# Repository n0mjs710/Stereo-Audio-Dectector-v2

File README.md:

# Stereo-Audio-Dectector-v2

Stereo Audio Detector: Precision rectifiers and integrators for driving VU displays.

This analog cirucit is intended to handle "front-end" conditioning for VU meters, but could be used for any low-frequency analog AC signal where the envelope of the waveform is of interest. The schmatic has several notes for changing values for different purposes.

The original intention was as VU meter front-end for Arduino or Teensy microcontrollers to use to "talk" to the Stereo VU Meter display, also published under my github account.

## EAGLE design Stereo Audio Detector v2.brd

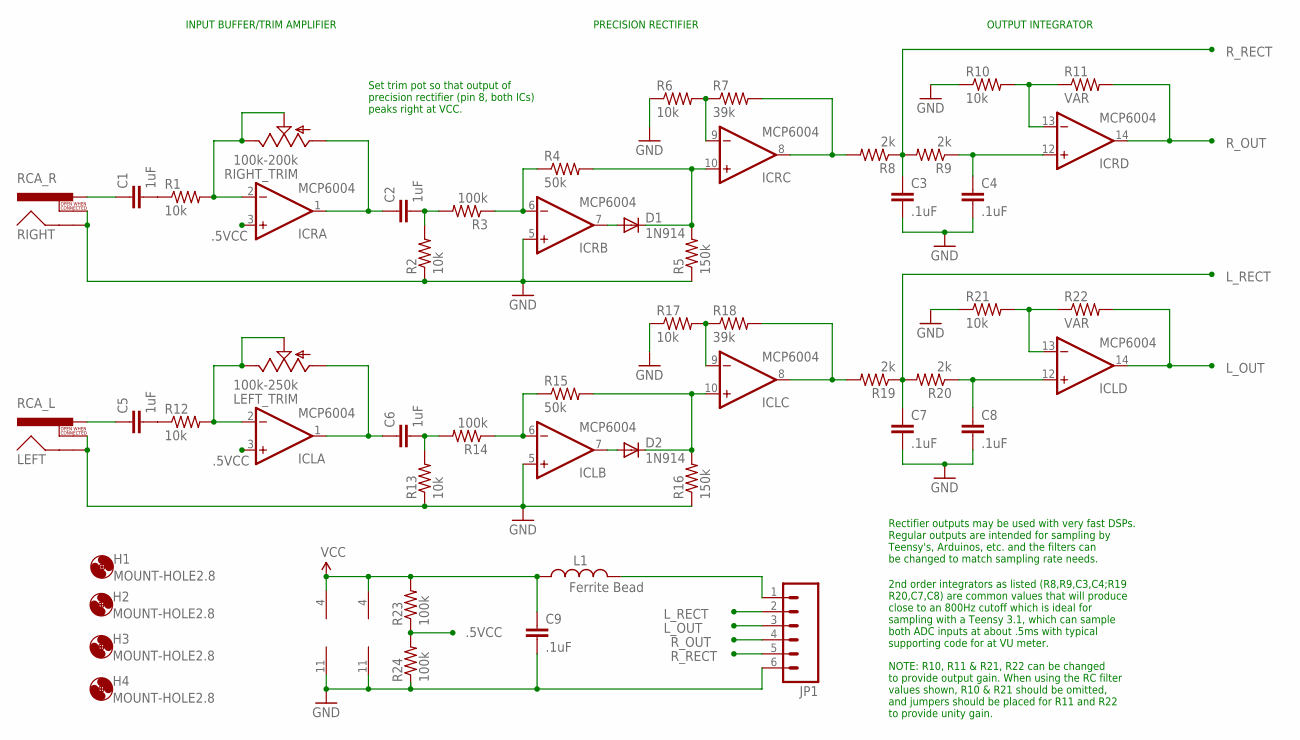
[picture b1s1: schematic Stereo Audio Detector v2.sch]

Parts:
C1, C2, C5, C6: 1uF; C2.5-2
C3, C4, C7, C8, C9: .1uF; C2.5-2
D1, D2: 1N914; D-5
H1, H2, H3, H4: MOUNT-HOLE2.8; 2,8
ICL: MCP6004; DIL14
ICR: MCP6004; DIL14
JP1: M06SIP; 1X06
L1: Ferrite Bead; AXIAL-0.3
LEFT: RCA_L; RCA
LEFT_TRIM: 100k-250k; CT6
R1, R2, R6, R10, R12, R13, R17, R21: 10k; AXIAL-0.3
R3, R14, R23, R24: 100k; AXIAL-0.3
R4, R15: 50k; AXIAL-0.3
R5, R16: 150k; AXIAL-0.3
R7, R18: 39k; AXIAL-0.3
R8, R9, R19, R20: 2k; AXIAL-0.3
R11, R22: VAR; AXIAL-0.3
RIGHT: RCA_R; RCA
RIGHT_TRIM: 100k-200k; CT6

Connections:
.5VCC: ICL.3 (+IN), ICR.3 (+IN), R23.P$1 (1), R24.P$2 (2)
GND: C3.2, C4.2, C7.2, C8.2, C9.2, ICL.5 (+IN), ICL.11 (V-), ICR.5 (+IN), ICR.11 (V-), JP1.6, LEFT.SHELL, LEFT.SWITCH, R2.P$1 (1), R5.P$1 (1), R6.P$1 (1), R10.P$1 (1), R13.P$1 (1), R16.P$1 (1), R17.P$1 (1), R21.P$1 (1), R24.P$1 (1), RIGHT.SHELL, RIGHT.SWITCH
IN_L: C1.1, RIGHT.PIN
IN_R: C5.1, LEFT.PIN
L_OUT: ICL.14 (OUT), JP1.3, R22.P$2 (2)
L_RECT: C7.1, JP1.2, R19.P$1 (1), R20.P$2 (2)
unnamed: C5.2, R12.P$1 (1)
unnamed: C1.2, R1.P$1 (1)
unnamed: JP1.1, L1.P$2 (2)
unnamed: ICR.2 (-IN), R1.P$2 (2), RIGHT_TRIM.E, RIGHT_TRIM.S
unnamed: C2.2, R2.P$2 (2), R3.P$2 (2)
unnamed: C2.1, ICR.1 (OUT), RIGHT_TRIM.A
unnamed: ICL.2 (-IN), LEFT_TRIM.E, LEFT_TRIM.S, R12.P$2 (2)
unnamed: ICR.6 (-IN), R3.P$1 (1), R4.P$1 (1)
unnamed: D1.C, ICR.10 (+IN), R4.P$2 (2), R5.P$2 (2)
unnamed: ICR.8 (OUT), R7.P$2 (2), R8.P$2 (2)
unnamed: ICR.9 (-IN), R6.P$2 (2), R7.P$1 (1)
unnamed: D1.A, ICR.7 (OUT)
unnamed: C4.1, ICR.12 (+IN), R9.P$1 (1)
unnamed: ICR.13 (-IN), R10.P$2 (2), R11.P$1 (1)
unnamed: C6.1, ICL.1 (OUT), LEFT_TRIM.A
unnamed: C6.2, R13.P$2 (2), R14.P$2 (2)
unnamed: ICL.6 (-IN), R14.P$1 (1), R15.P$1 (1)
unnamed: ICL.9 (-IN), R17.P$2 (2), R18.P$1 (1)
unnamed: ICL.8 (OUT), R18.P$2 (2), R19.P$2 (2)
unnamed: D2.A, ICL.7 (OUT)
unnamed: D2.C, ICL.10 (+IN), R15.P$2 (2), R16.P$2 (2)
unnamed: ICL.13 (-IN), R21.P$2 (2), R22.P$1 (1)
unnamed: C8.1, ICL.12 (+IN), R20.P$1 (1)
R_OUT: ICR.14 (OUT), JP1.4, R11.P$2 (2)
R_RECT: C3.1, JP1.5, R8.P$1 (1), R9.P$2 (2)
VCC: C9.1, ICL.4 (V+), ICR.4 (V+), L1.P$1 (1), R23.P$2 (2)

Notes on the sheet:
NOTE: R10, R11 & R21, R22 can be changed to provide output gain. When using the RC filter values shown, R10 & R21 should be omitted, and jumpers should be placed for R11 and R22 to provide unity gain.
2nd order integrators as listed (R8,R9,C3,C4;R19 R20,C7,C8) are common values that will produce close to an 800Hz cutoff which is ideal for sampling with a Teensy 3.1, which can sample both ADC inputs at about .5ms with typical supporting code for at VU meter.
Rectifier outputs may be used with very fast DSPs. Regular outputs are intended for sampling by Teensy's, Arduinos, etc. and the filters can be changed to match sampling rate needs.
INPUT BUFFER/TRIM AMPLIFIER
PRECISION RECTIFIER
OUTPUT INTEGRATOR
Set trim pot so that output of precision rectifier (pin 8, both ICs) peaks right at VCC.

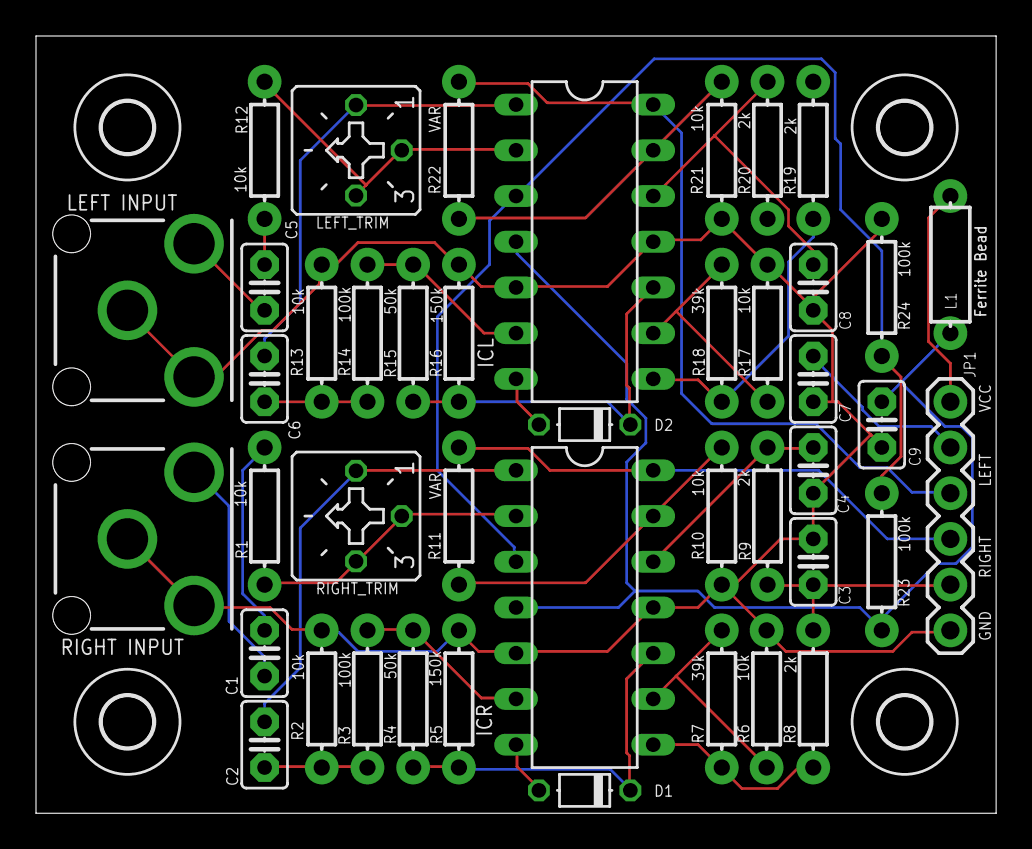
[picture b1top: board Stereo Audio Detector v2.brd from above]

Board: 2 copper layers, 53.3 x 43.2 mm, 47 parts (0 on the bottom side), 32 nets.

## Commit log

2015-04-11 Initial Upload

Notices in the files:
parts and their libraries:
SparkFun: Licensing: CC v3.0 Share-Alike You are welcome to use this library for commercial purposes.
